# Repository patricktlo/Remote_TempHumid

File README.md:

# Remote TempHumid sensor

Using a simple STM32F030 MCU with a temperature sensor (TBD) and a relative humidity sensor (TBD), coupled with optional Wifi (ESP-01) or LoRa (RA-01) connectivity.

Initially this project is aimed to measure the conditions of a wine cellar, ideal stats include temperature around 12 C and RH 50-80%. But this board is designed to be versatile and could be used anywhere.

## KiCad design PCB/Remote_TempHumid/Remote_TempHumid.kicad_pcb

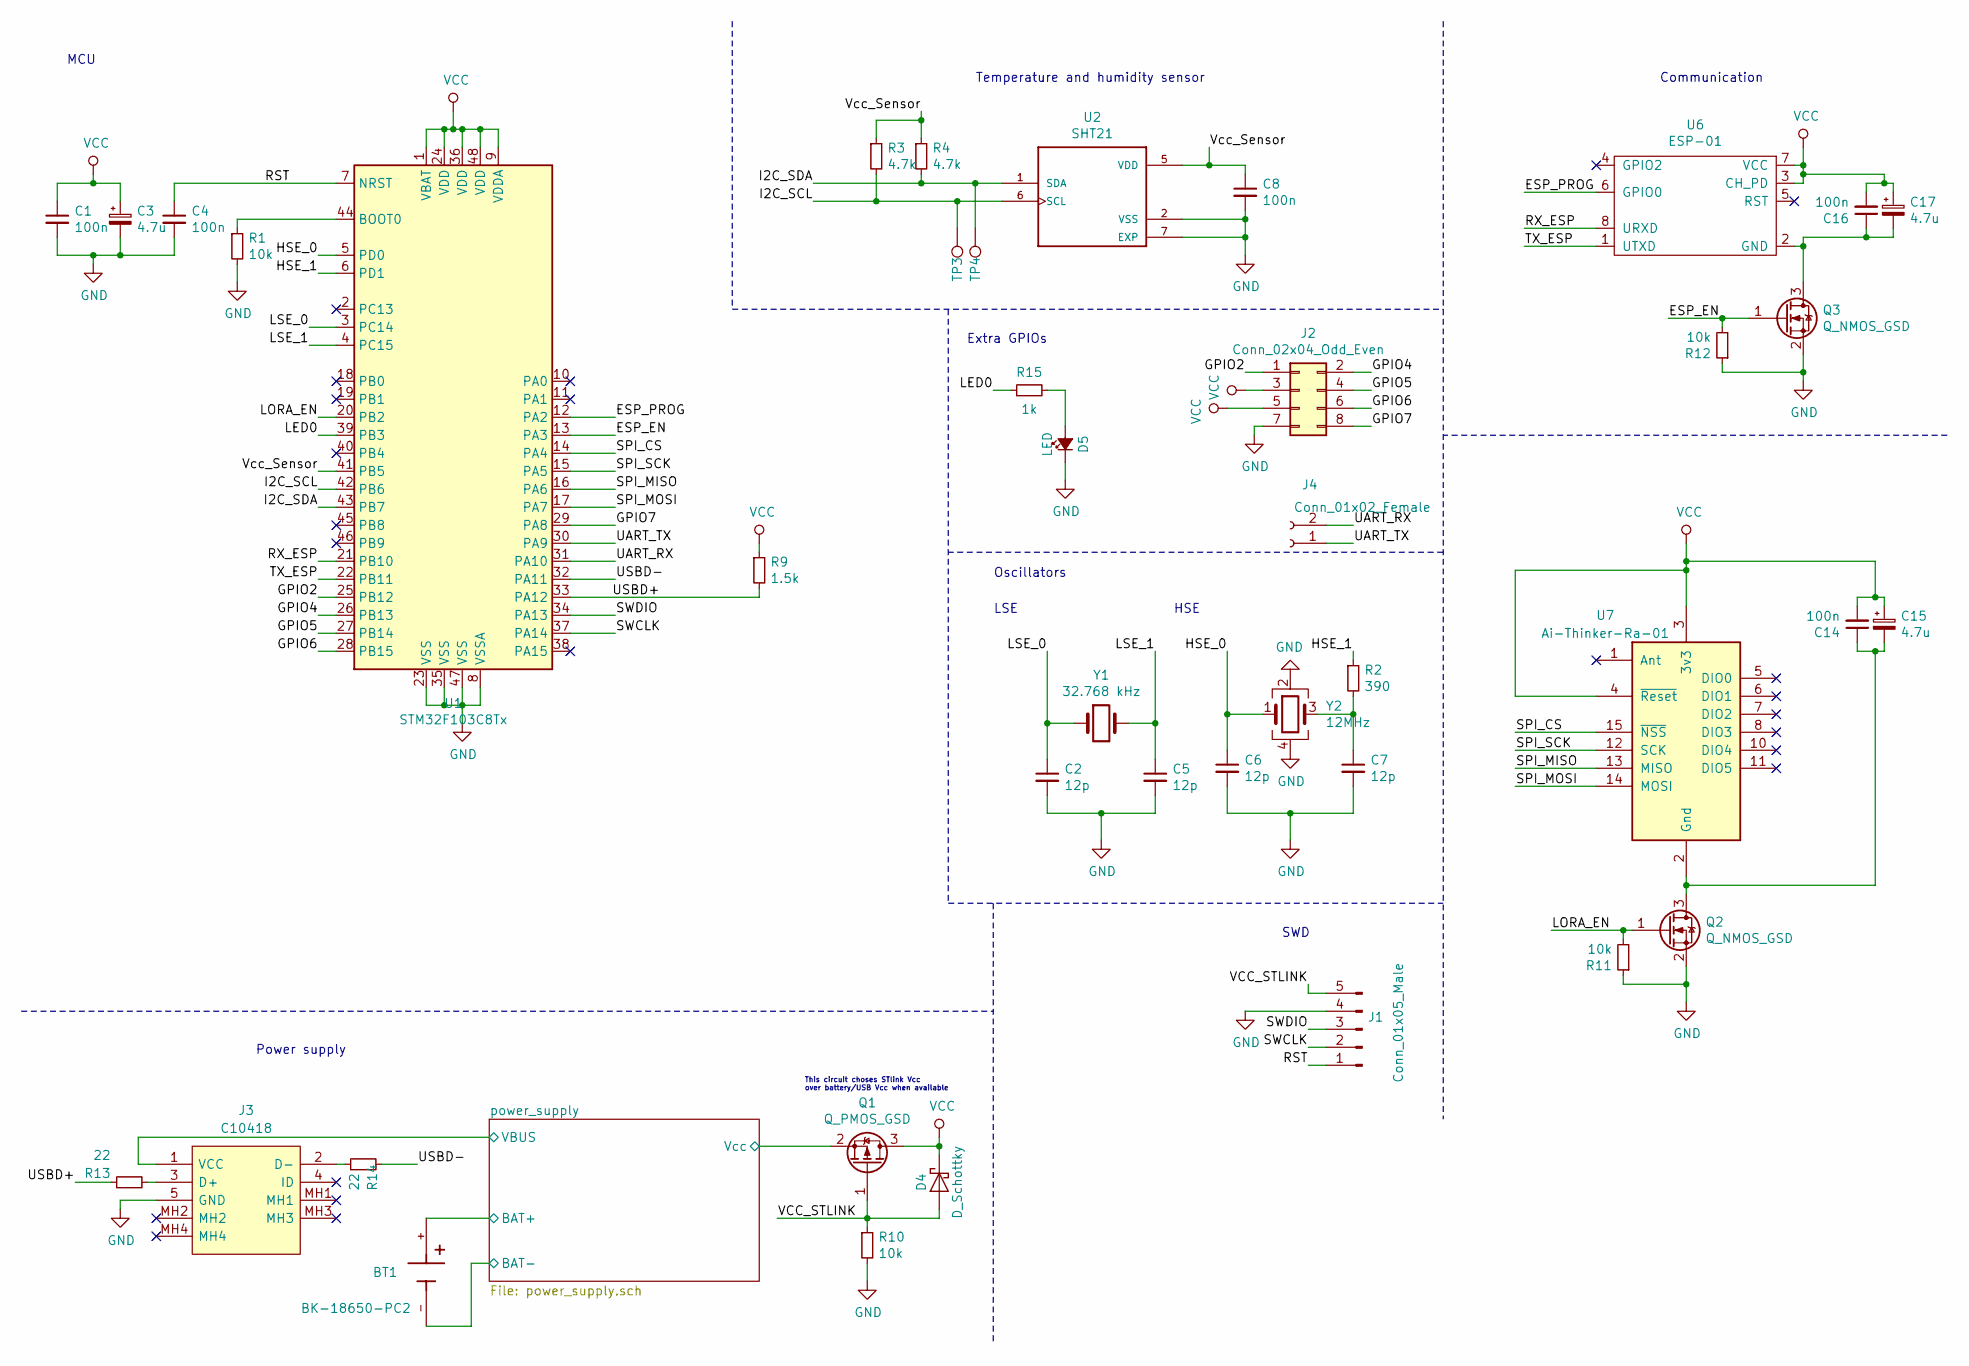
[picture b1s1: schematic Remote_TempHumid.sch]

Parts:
BT1: BK-18650-PC2; BAT_BK-18650-PC2
C1, C4, C8, C14, C16: 100n; C_0603_1608Metric; LCSC C14663
C2, C5, C6, C7: 12p; C_0603_1608Metric; LCSC C38523
C3, C15, C17: 4.7u; C_0603_1608Metric; LCSC C19666
D4: D_Schottky; D_SMA; LCSC C2480
D5: LED; LED_0603_1608Metric; LCSC C2290
J1: Conn_01x05_Male; PinHeader_1x05_P2.54mm_Vertical
J2: Conn_02x04_Odd_Even; PinHeader_2x04_P2.54mm_Vertical
J3: C10418; LCSC C10418
J4: Conn_01x02_Female; PinSocket_1x02_P2.54mm_Vertical
Q1: Q_PMOS_GSD; SOT-23W; LCSC C15127
Q2, Q3: Q_NMOS_GSD; SOT-23W; LCSC C20917
R1, R10, R11, R12: 10k; R_0603_1608Metric; LCSC C25804
R2: 390; R_0603_1608Metric; LCSC C23151
R3, R4: 4.7k; R_0603_1608Metric; LCSC C23162
R9: 1.5k; R_0603_1608Metric; LCSC C22843
R13, R14: 22; R_0603_1608Metric; LCSC C23345
R15: 1k; R_0603_1608Metric; LCSC C21190
TP3, TP4: TestPoint; TestPoint_Pad_D1.5mm
U1: STM32F103C8Tx; LQFP-48_7x7mm_P0.5mm; LCSC C8734
U2: SHT21; DFN300X300X110-7N; LCSC C84828
U6: ESP-01
U7: Ai-Thinker-Ra-01; Ai-Thinker-Ra-01-LoRa
Y1: 32.768 kHz; Crystal_SMD_3215-2Pin_3.2x1.5mm; LCSC C32346
Y2: 12MHz; Crystal_SMD_3225-4Pin_3.2x2.5mm; LCSC C9002

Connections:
/ESP_EN: Q3.1 (G), R12.2, U1.13 (PA3)
/ESP_PROG: U1.12 (PA2), U6.6 (GPIO0)
/GPIO2: J2.1, U1.25 (PB12)
/GPIO4: J2.2, U1.26 (PB13)
/GPIO5: J2.4, U1.27 (PB14)
/GPIO6: J2.6, U1.28 (PB15)
/GPIO7: J2.8, U1.29 (PA8)
/HSE_0: C6.1, U1.5 (PD0), Y2.1
/HSE_1: R2.1, U1.6 (PD1)
/I2C_SCL: R3.2, TP3.1, U1.42 (PB6), U2.6 (SCL)
/I2C_SDA: R4.2, TP4.1, U1.43 (PB7), U2.1 (SDA)
/LED0: R15.1, U1.39 (PB3)
/LORA_EN: Q2.1 (G), R11.2, U1.20 (PB2)
/LSE_0: C2.1, U1.3 (PC14), Y1.1
/LSE_1: C5.1, U1.4 (PC15), Y1.2
/RST: C4.1, J1.1, U1.7 (NRST)
/RX_ESP: U1.21 (PB10), U6.8 (URXD)
/SPI_CS: U1.14 (PA4), U7.15 (~NSS)
/SPI_MISO: U1.16 (PA6), U7.13 (MISO)
/SPI_MOSI: U1.17 (PA7), U7.14 (MOSI)
/SPI_SCK: U1.15 (PA5), U7.12 (SCK)
/SWCLK: J1.2, U1.37 (PA14)
/SWDIO: J1.3, U1.34 (PA13)
/TX_ESP: U1.22 (PB11), U6.1 (UTXD)
/UART_RX: J4.2, U1.31 (PA10)
/UART_TX: J4.1, U1.30 (PA9)
/USBD+: R9.2, R13.1, U1.33 (PA12)
/USBD-: R14.2, U1.32 (PA11)
/VCC_STLINK: D4.2 (A), J1.5, Q1.1 (G), R10.1
/Vcc_Sensor: C8.1, R3.1, R4.1, U1.41 (PB5), U2.5 (VDD)
/power_supply/BAT+: BT1.+; also elsewhere on the board
/power_supply/BAT-: BT1.-; also elsewhere on the board
/power_supply/VBUS: J3.1 (VCC); also elsewhere on the board
/power_supply/Vcc: Q1.2 (S); also elsewhere on the board
GND: C1.2, C2.2, C3.2, C4.2, C5.2, C6.2, C7.2, C8.2, D5.1 (K), J1.4, J2.7, J3.5 (GND), Q2.2 (S), Q3.2 (S), R1.2, R10.2, R11.1, R12.1, U1.8 (VSSA), U1.23 (VSS), U1.35 (VSS), U1.47 (VSS), U2.2 (VSS), U2.7 (EXP), Y2.2, Y2.4; also elsewhere on the board
unnamed: C7.1, R2.2, Y2.3
unnamed: C14.1, C15.2, Q2.3 (D), U7.2 (Gnd), U7.9 (Gnd), U7.16 (Gnd)
unnamed: C16.1, C17.2, Q3.3 (D), U6.2 (GND)
unnamed: D5.2 (A), R15.2
unnamed: J3.2 (D-), R14.1
unnamed: J3.3 (D+), R13.2
unnamed: R1.1, U1.44 (BOOT0)
VCC: C1.1, C3.1, C14.2, C15.1, C16.2, C17.1, D4.1 (K), J2.3, J2.5, Q1.3 (D), R9.1, U1.1 (VBAT), U1.9 (VDDA), U1.24 (VDD), U1.36 (VDD), U1.48 (VDD), U6.3 (CH_PD), U6.7 (VCC), U7.3 (3v3), U7.4 (~Reset)

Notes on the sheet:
Communication
Temperature and humidity sensor
MCU
Power supply
SWD
Oscillators
LSE
HSE
This circuit choses STlink Vcc over battery/USB Vcc when available
Extra GPIOs

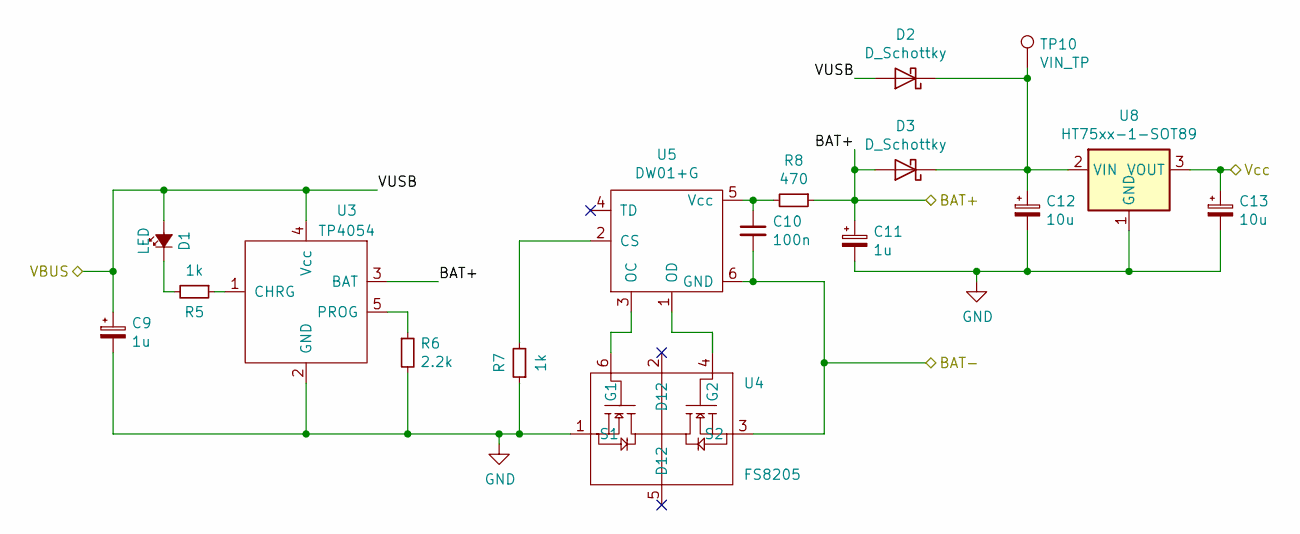
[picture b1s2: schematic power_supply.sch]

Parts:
C9, C11: 1u; C_0805_2012Metric; LCSC C28323
C10: 100n; C_0603_1608Metric; LCSC C14663
C12, C13: 10u; C_0805_2012Metric; LCSC C15850
D1: LED; LED_0603_1608Metric; LCSC C72041
D2, D3: D_Schottky; D_SMA; LCSC C2480
R5, R7: 1k; R_0603_1608Metric; LCSC C21190
R6: 2.2k; R_0603_1608Metric; LCSC C4190
R8: 470; R_0603_1608Metric; LCSC C23179
TP10: VIN_TP; TestPoint_Pad_D1.5mm
U3: TP4054; SOT-23-5; LCSC C32574
U4: FS8205; SOT-23-6; LCSC C32254
U5: DW01+G; SOT-23-6; LCSC C14213
U8: HT75xx-1-SOT89; SOT-89-3; LCSC C14289

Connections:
/power_supply/BAT+: C11.1, D3.2 (A), R8.1, U3.3 (BAT); also elsewhere on the board
/power_supply/BAT-: C10.2, U4.3 (S2), U5.6 (GND); also elsewhere on the board
/power_supply/VBUS: C9.1, D1.2 (A), D2.2 (A), U3.4 (Vcc); also elsewhere on the board
/power_supply/Vcc: C13.1, U8.3 (VOUT); also elsewhere on the board
GND: C9.2, C11.2, C12.2, C13.2, R6.2, R7.1, U3.2 (GND), U4.1 (S1), U8.1 (GND); also elsewhere on the board
unnamed: C10.1, R8.2, U5.5 (Vcc)
unnamed: C12.1, D2.1 (K), D3.1 (K), TP10.1, U8.2 (VIN)
unnamed: D1.1 (K), R5.2
unnamed: R5.1, U3.1 (CHRG)
unnamed: R6.1, U3.5 (PROG)
unnamed: R7.2, U5.2 (CS)
unnamed: U4.4 (G2), U5.1 (OD)
unnamed: U4.6 (G1), U5.3 (OC)

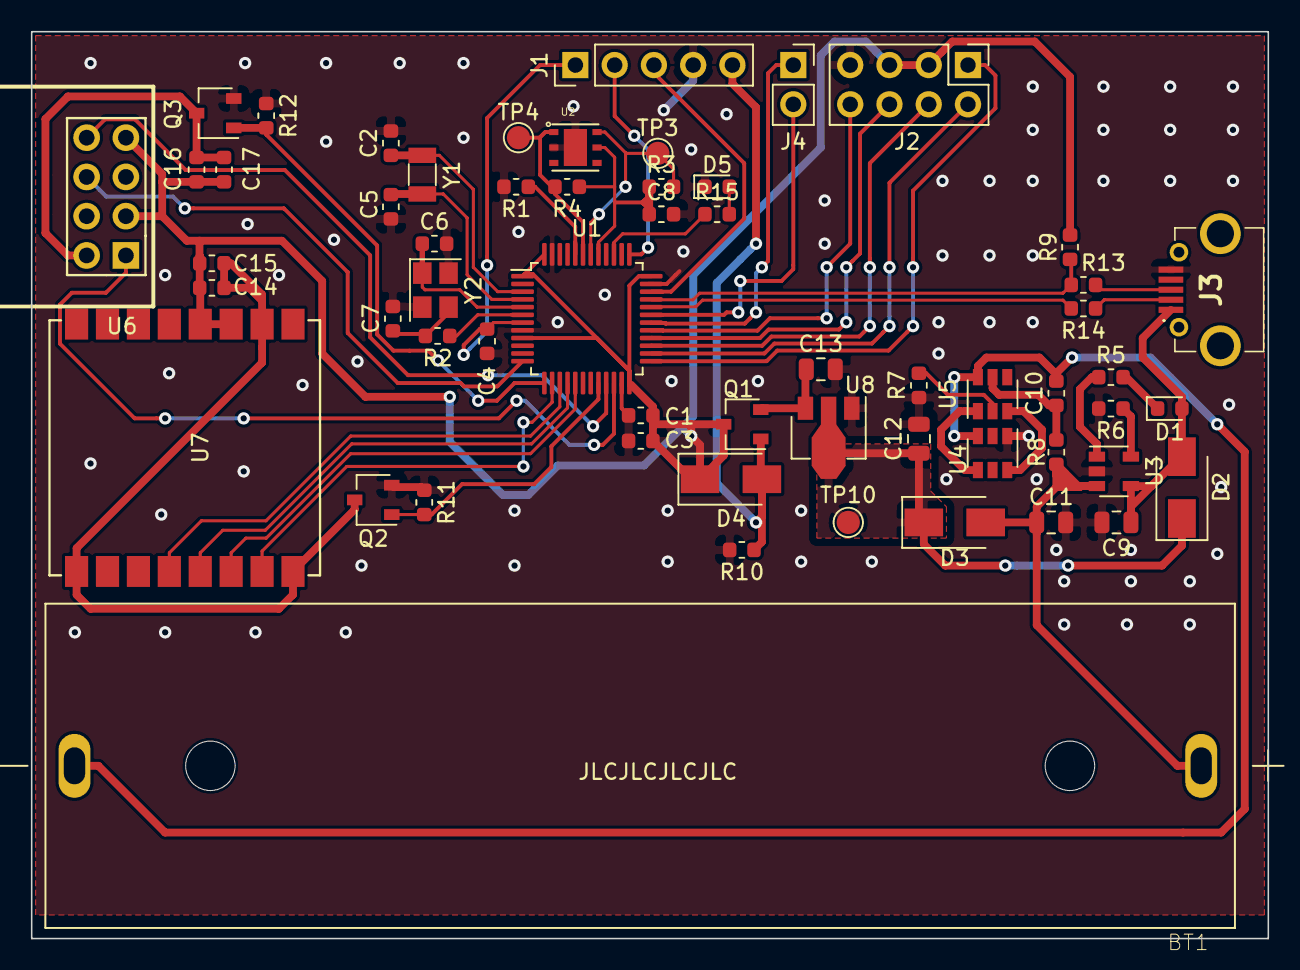
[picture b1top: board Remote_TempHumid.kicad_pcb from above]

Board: 2 copper layers, 80.0 x 58.7 mm, 58 parts (0 on the bottom side), 51 nets.

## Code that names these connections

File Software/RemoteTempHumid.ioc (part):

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Mcu.Name=STM32F103C(8-B)Tx
Mcu.Package=LQFP48
Mcu.UserName=STM32F103C8Tx
PA10.Mode=Asynchronous
PA10.Signal=USART1_RX
PA11.Mode=Device
PA11.Signal=USB_DM
PA12.Mode=Device
PA12.Signal=USB_DP
PA13.Mode=Serial_Wire
PA13.Signal=SYS_JTMS-SWDIO
PA14.Mode=Serial_Wire
PA14.Signal=SYS_JTCK-SWCLK
PA3.GPIOParameters=GPIO_Label
PA3.GPIO_Label=LORA_EN
PA3.Signal=GPIO_Output
PA4.Mode=NSS_Signal_Hard_Output
PA4.Signal=SPI1_NSS
PA5.Mode=Full_Duplex_Master
PA5.Signal=SPI1_SCK
PA6.Mode=Full_Duplex_Master
PA6.Signal=SPI1_MISO
PA7.Mode=Full_Duplex_Master
PA7.Signal=SPI1_MOSI
PA9.Mode=Asynchronous
PA9.Signal=USART1_TX
PB10.Mode=Asynchronous
PB10.Signal=USART3_TX
PB11.Mode=Asynchronous
PB11.Signal=USART3_RX
PB12.GPIOParameters=GPIO_Label
PB12.GPIO_Label=ESP_PROG
PB12.Signal=GPIO_Output
PB2.GPIOParameters=GPIO_Label
PB2.GPIO_Label=ESP_EN
PB2.Signal=GPIO_Output
PB3.GPIOParameters=GPIO_Label
PB3.GPIO_Label=LED0
PB3.Signal=GPIO_Output
PB5.GPIOParameters=GPIO_Label
PB5.GPIO_Label=Vcc_Sensor
PB5.Signal=GPIO_Output
PB6.Mode=I2C
PB6.Signal=I2C1_SCL
PB7.Mode=I2C
PB7.Signal=I2C1_SDA
PC14-OSC32_IN.Mode=LSE-External-Oscillator
PC14-OSC32_IN.Signal=RCC_OSC32_IN
PC15-OSC32_OUT.Mode=LSE-External-Oscillator
PC15-OSC32_OUT.Signal=RCC_OSC32_OUT
PD0-OSC_IN.Mode=HSE-External-Oscillator
PD0-OSC_IN.Signal=RCC_OSC_IN
PD1-OSC_OUT.Mode=HSE-External-Oscillator
PD1-OSC_OUT.Signal=RCC_OSC_OUT
RCC.HSE_VALUE=12000000
RCC.SYSCLKFreq_VALUE=48000000
RCC.SYSCLKSource=RCC_SYSCLKSOURCE_PLLCLK
board=custom

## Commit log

2020-05-10 started PCB and cubemx project
2021-05-05 up to date with old ubuntu
